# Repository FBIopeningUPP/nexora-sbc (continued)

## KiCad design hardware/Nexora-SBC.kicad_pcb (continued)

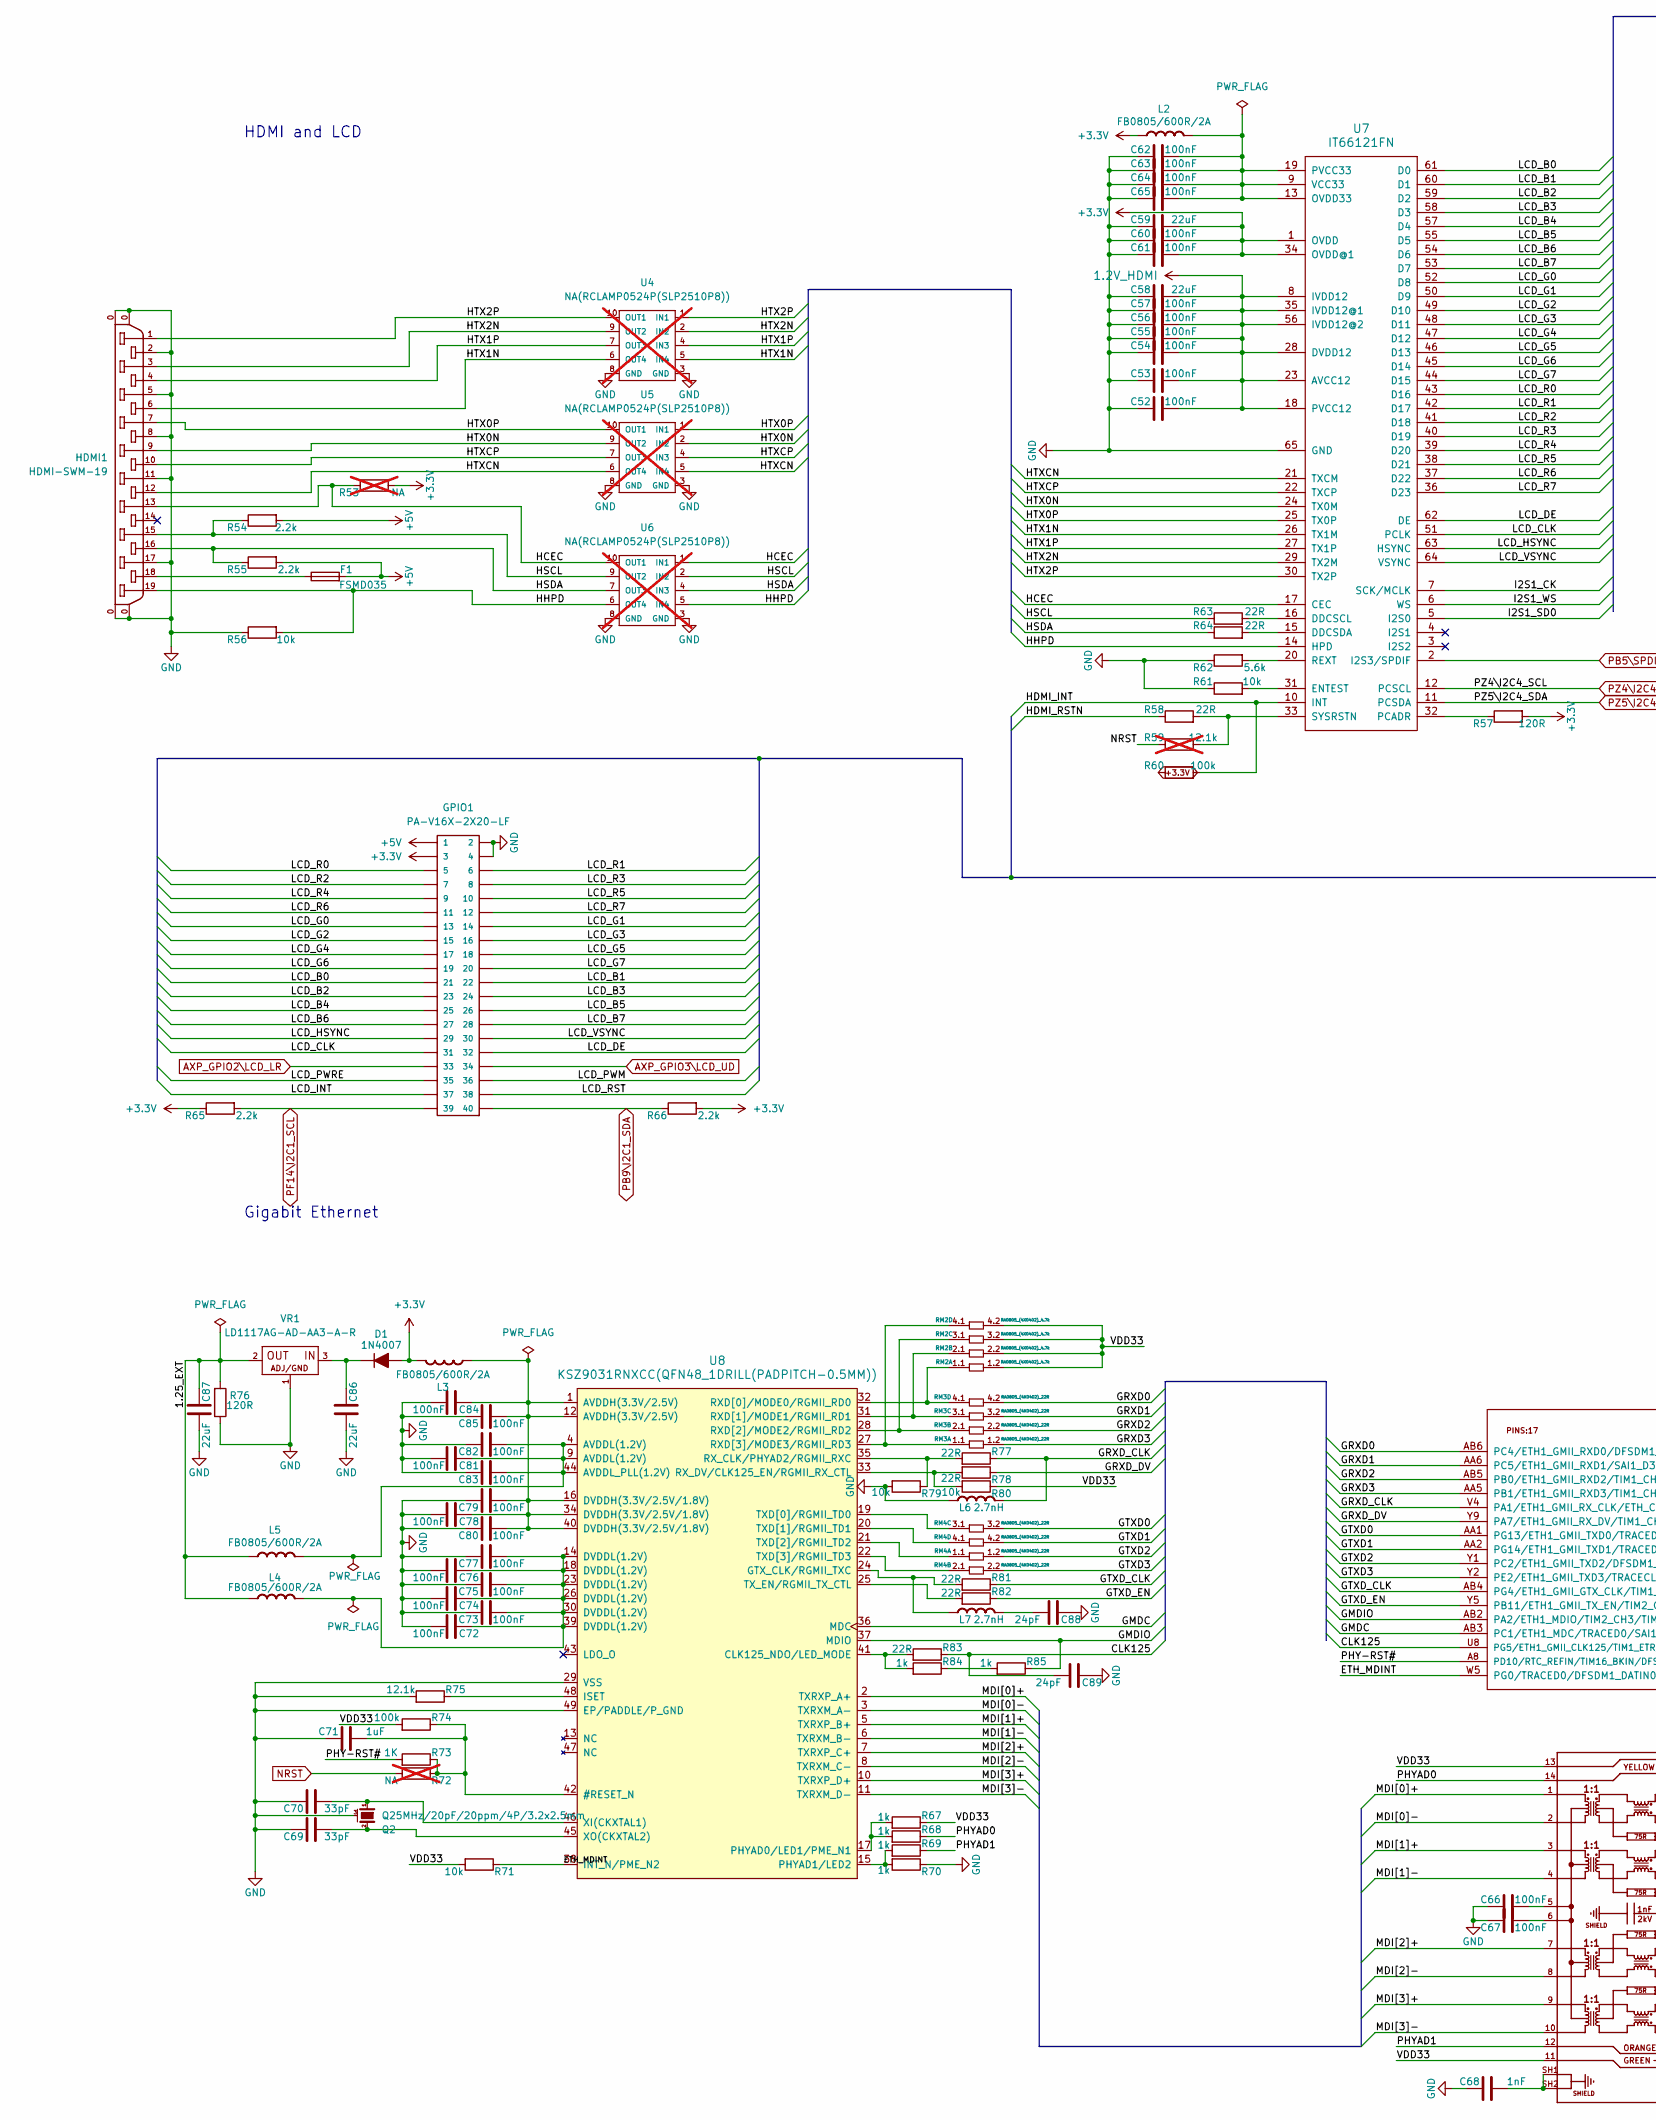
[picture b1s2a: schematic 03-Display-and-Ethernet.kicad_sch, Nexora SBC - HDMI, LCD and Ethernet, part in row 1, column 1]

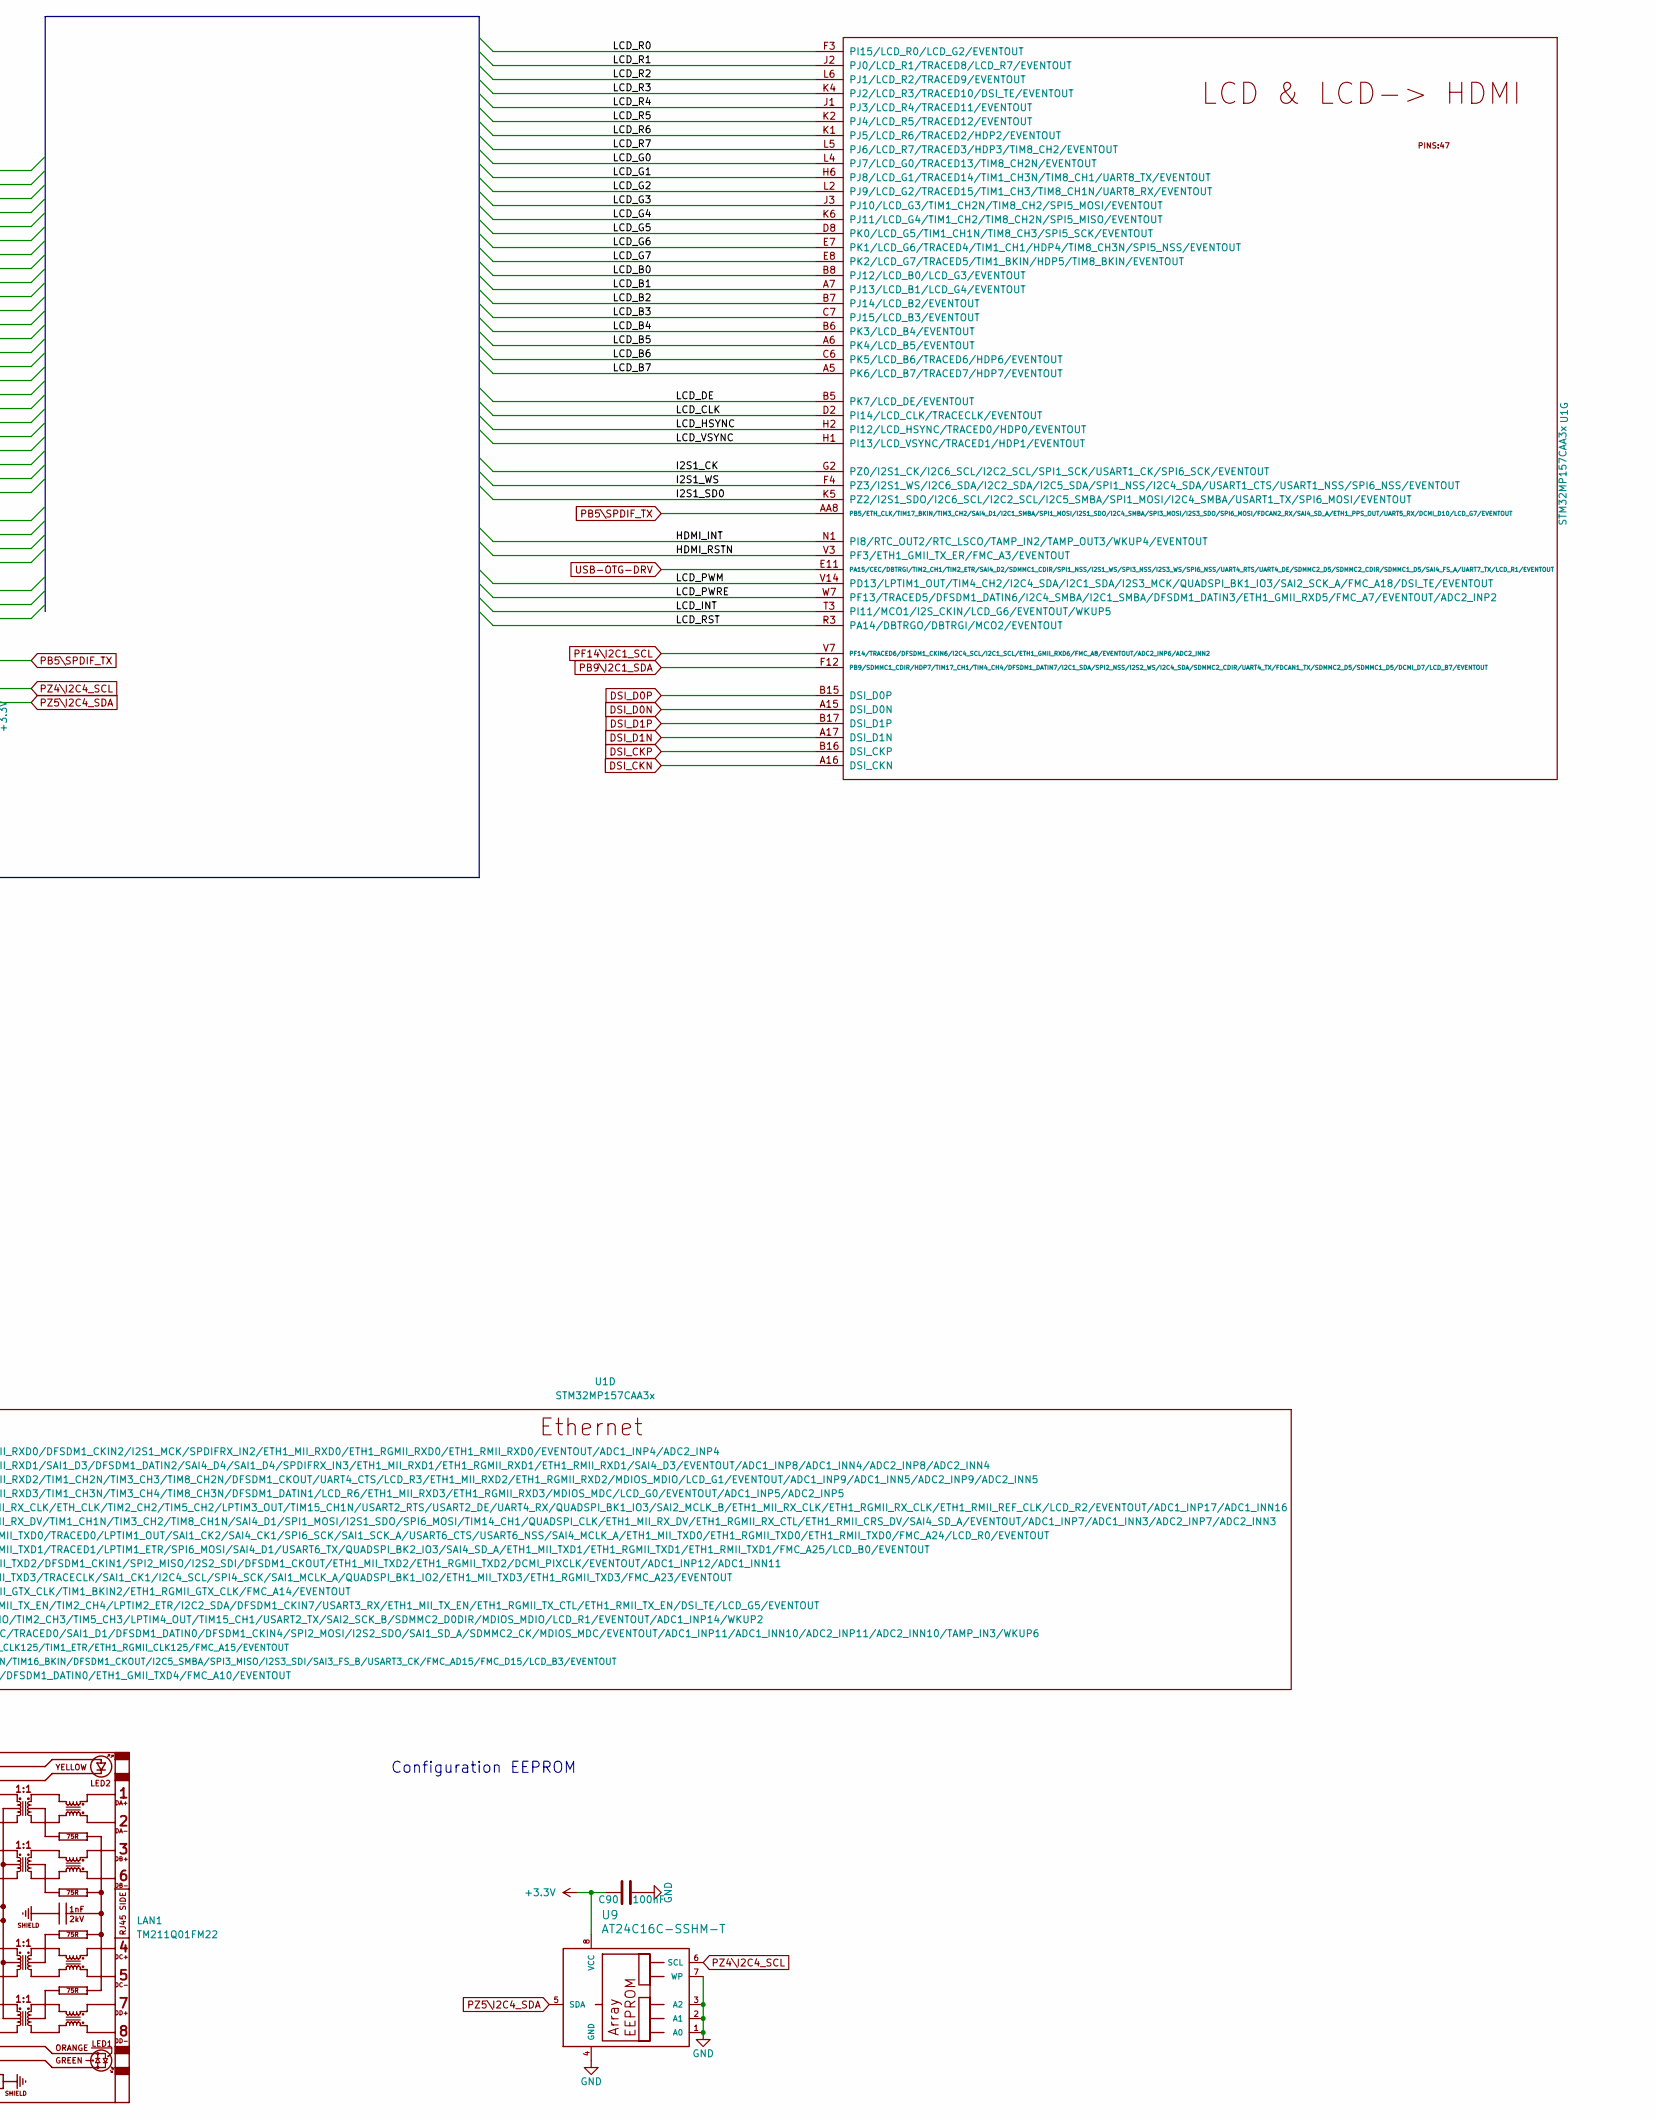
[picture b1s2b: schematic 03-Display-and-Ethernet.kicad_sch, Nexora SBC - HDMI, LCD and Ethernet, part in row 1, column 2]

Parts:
C52, C53, C54, C55, C56, C57, C60, C61, C62, C63, C64, C65, C66, C67, C72, C73, C74, C75, C76, C77, C78, C79, C80, C81, C82, C83, C84, C85, C90: 100nF; C_0402_1005Metric
C58, C59, C86, C87: 22uF; C_0402_1005Metric
C68: 1nF; C_0402_1005Metric
C69, C70: 33pF; C_0402_1005Metric
C71: 1uF; C_0402_1005Metric
C88, C89: 24pF; C_0402_1005Metric
D1: 1N4007; D_SMA
F1: FSMD035; FUSE-1206
GPIO1: PA-V16X-2X20-LF; GPH127SMT-02X20(PA-V16X-2X20-LF)
HDMI1: HDMI-SWM-19
L2, L3, L4, L5: FB0805/600R/2A; L_0805_2012Metric; Rating A
L6, L7: 2.7nH; L_0402_1005Metric; Rating A
LAN1: TM211Q01FM22
Q2: Q25MHz/20pF/20ppm/4P/3.2x2.5mm; TSX-3.2x2.5mm_GND(3)
R53, R72: NA; R_0402_1005Metric; not fitted
R54, R55, R65, R66: 2.2k; R_0402_1005Metric
R56, R61, R71, R79, R80: 10k; R_0402_1005Metric
R57, R76: 120R; R_0402_1005Metric
R58, R63, R64, R77, R78, R81, R82, R83: 22R; R_0402_1005Metric
R59: 12.1k; R_0402_1005Metric; not fitted
R60, R74: 100k; R_0402_1005Metric
R62: 5.6k; R_0402_1005Metric
R67, R68, R69, R70, R84, R85: 1k; R_0402_1005Metric
R73: 1K; R_0402_1005Metric
R75: 12.1k; R_0402_1005Metric
RM2: RA0805_(4X0402)_4.7k; RA0805_(4X0402)_xx_BIGGEROUTPADS
RM3, RM4: RA0805_(4X0402)_22R; RA0805_(4X0402)_xx_BIGGEROUTPADS
U1: STM32MP157CAA3x; LFBGA-448(Pitch-0.8mm_Pad-0.4mm_18x18x1.27mm)
U4, U5, U6: NA(RCLAMP0524P(SLP2510P8)); SLP2510P8_TEST; not fitted
U7: IT66121FN; QFN64_9x9mm_Pitch_0.5mm_65PAD_4.5mm
U8: KSZ9031RNXCC(QFN48_1DRILL(PADPITCH-0.5MM)); QFN48_1DRILL(PADPITCH-0.5MM)
U9: AT24C16C-SSHM-T; SOIC-8_3.9x4.9mm_P1.27mm
VR1: LD1117AG-AD-AA3-A-R; SOT223

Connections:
1.2V_HDMI: C52.2, C53.2, C54.2, C55.2, C56.2, C57.2, C58.2, U7.8 (IVDD12), U7.18 (PVCC12), U7.23 (AVCC12), U7.28 (DVDD12), U7.35 (IVDD12@1), U7.56 (IVDD12@2); also elsewhere on the board
+3.3V: C59.2, C60.2, C61.2, C90.1, D1.2 (A), GPIO1.3, L2.1 (+), L3.1 (+), R53.1, R57.1, R60.2, R65.2, R66.1, U7.1 (OVDD), U7.34 (OVDD@1), U9.8 (VCC); also elsewhere on the board
+5V: F1.2, GPIO1.1, R54.1, R55.1; also elsewhere on the board
/HDMI, LCD and Ethernet/1.25_EXT: C87.1, L4.1 (+), L5.1 (+), R76.1, VR1.2 (OUT)
/HDMI, LCD and Ethernet/CLK125: C89.2, R83.2, U1.U8 (PG5/ETH1_GMII_CLK125/TIM1_ETR/ETH1_RGMI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)
/HDMI, LCD and Ethernet/ETH_MDINT: R71.2, U1.W5 (PG0/TRACED0/DFSDM1_DATIN0/ETH1_GMII_TXD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), U8.38 (INT_N/PME_N2)
/HDMI, LCD and Ethernet/GMDC: U1.AB3 (PC1/ETH1_MDC/TRACED0/SAI1_D1/DFSDM1_DAT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), U8.36 (MDC)
/HDMI, LCD and Ethernet/GMDIO: R85.2, U1.AB2 (PA2/ETH1_MDIO/TIM2_CH3/TIM5_CH3/LPTIM4_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), U8.37 (MDIO)
/HDMI, LCD and Ethernet/GRXD0: RM3.4.2, U1.AB6 (PC4/ETH1_GMII_RXD0/DFSDM1_CKIN2/I2S1_MC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)
/HDMI, LCD and Ethernet/GRXD1: RM3.3.2, U1.AA6 (PC5/ETH1_GMII_RXD1/SAI1_D3/DFSDM1_DATIN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)
/HDMI, LCD and Ethernet/GRXD2: RM3.2.2, U1.AB5 (PB0/ETH1_GMII_RXD2/TIM1_CH2N/TIM3_CH3/T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)
/HDMI, LCD and Ethernet/GRXD3: RM3.1.2, U1.AA5 (PB1/ETH1_GMII_RXD3/TIM1_CH3N/TIM3_CH4/T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)
/HDMI, LCD and Ethernet/GRXD_CLK: L6.2 (-), R77.2, U1.V4 (PA1/ETH1_GMII_RX_CLK/ETH_CLK/ТIM2_CH2/T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)
/HDMI, LCD and Ethernet/GRXD_DV: R78.2, U1.Y9 (PA7/ETH1_GMII_RX_DV/TIM1_CH1N/TIM3_CH2/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)
/HDMI, LCD and Ethernet/GTXD0: RM4.3.2, U1.AA1 (PG13/ETH1_GMII_TXD0/TRACED0/LPTIM1_OUT/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)
/HDMI, LCD and Ethernet/GTXD1: RM4.4.2, U1.AA2 (PG14/ETH1_GMII_TXD1/TRACED1/LPTIM1_ETR/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)
/HDMI, LCD and Ethernet/GTXD2: RM4.1.2, U1.Y1 (PC2/ETH1_GMII_TXD2/DFSDM1_CKIN1/SPI2_MI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)
/HDMI, LCD and Ethernet/GTXD3: RM4.2.2, U1.Y2 (PE2/ETH1_GMII_TXD3/TRACECLK/SAI1_CK1/I2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)
/HDMI, LCD and Ethernet/GTXD_CLK: R81.2, U1.AB4 (PG4/ETH1_GMII_GTX_CLK/TIM1_BKIN2/ETH1_R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)
/HDMI, LCD and Ethernet/GTXD_EN: R82.2, U1.Y5 (PB11/ETH1_GMII_TX_EN/TIM2_CH4/LPTIM2_ET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)
/HDMI, LCD and Ethernet/HCEC: HDMI1.13, R53.2, U6.1 (IN1), U6.10 (OUT1), U7.17 (CEC)
/HDMI, LCD and Ethernet/HDMI_INT: R60.1, U1.N1 (PI8/RTC_OUT2/RTC_LSCO/TAMP_IN2/TAMP_OUT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), U7.10 (INT)
/HDMI, LCD and Ethernet/HDMI_RSTN: R58.2, U1.V3 (PF3/ETH1_GMII_TX_ER/FMC_A3/EVENTOUT)
/HDMI, LCD and Ethernet/HHPD: HDMI1.19, R56.1, U6.5 (IN4), U6.6 (OUT4), U7.14 (HPD)
/HDMI, LCD and Ethernet/HSCL: HDMI1.15, R54.2, R63.2, U6.2 (IN2), U6.9 (OUT2)
/HDMI, LCD and Ethernet/HSDA: HDMI1.16, R55.2, R64.2, U6.4 (IN3), U6.7 (OUT3)
/HDMI, LCD and Ethernet/HTX0N: HDMI1.9, U5.2 (IN2), U5.9 (OUT2), U7.24 (TX0M)
/HDMI, LCD and Ethernet/HTX0P: HDMI1.7, U5.1 (IN1), U5.10 (OUT1), U7.25 (TX0P)
/HDMI, LCD and Ethernet/HTX1N: HDMI1.6, U4.5 (IN4), U4.6 (OUT4), U7.26 (TX1M)
/HDMI, LCD and Ethernet/HTX1P: HDMI1.4, U4.4 (IN3), U4.7 (OUT3), U7.27 (TX1P)
/HDMI, LCD and Ethernet/HTX2N: HDMI1.3, U4.2 (IN2), U4.9 (OUT2), U7.29 (TX2M)
/HDMI, LCD and Ethernet/HTX2P: HDMI1.1, U4.1 (IN1), U4.10 (OUT1), U7.30 (TX2P)
/HDMI, LCD and Ethernet/HTXCN: HDMI1.12, U5.5 (IN4), U5.6 (OUT4), U7.21 (TXCM)
/HDMI, LCD and Ethernet/HTXCP: HDMI1.10, U5.4 (IN3), U5.7 (OUT3), U7.22 (TXCP)
/HDMI, LCD and Ethernet/I2S1_CK: U1.G2 (PZ0/I2S1_CK/I2C6_SCL/I2C2_SCL/SPI1_SCK/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), U7.7 (SCK/MCLK)
/HDMI, LCD and Ethernet/I2S1_SD0: U1.K5 (PZ2/I2S1_SDO/I2C6_SCL/I2C2_SCL/I2C5_SMB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), U7.5 (I2S0)
/HDMI, LCD and Ethernet/I2S1_WS: U1.F4 (PZ3/I2S1_WS/I2C6_SDA/I2C2_SDA/I2C5_SDA/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), U7.6 (WS)
/HDMI, LCD and Ethernet/LCD_B0: GPIO1.21, U1.B8 (PJ12/LCD_B0/LCD_G3/EVENTOUT), U7.61 (D0)
/HDMI, LCD and Ethernet/LCD_B1: GPIO1.22, U1.A7 (PJ13/LCD_B1/LCD_G4/EVENTOUT), U7.60 (D1)
/HDMI, LCD and Ethernet/LCD_B2: GPIO1.23, U1.B7 (PJ14/LCD_B2/EVENTOUT), U7.59 (D2)
/HDMI, LCD and Ethernet/LCD_B3: GPIO1.24, U1.C7 (PJ15/LCD_B3/EVENTOUT), U7.58 (D3)
/HDMI, LCD and Ethernet/LCD_B4: GPIO1.25, U1.B6 (PK3/LCD_B4/EVENTOUT), U7.57 (D4)
/HDMI, LCD and Ethernet/LCD_B5: GPIO1.26, U1.A6 (PK4/LCD_B5/EVENTOUT), U7.55 (D5)
/HDMI, LCD and Ethernet/LCD_B6: GPIO1.27, U1.C6 (PK5/LCD_B6/TRACED6/HDP6/EVENTOUT), U7.54 (D6)
/HDMI, LCD and Ethernet/LCD_B7: GPIO1.28, U1.A5 (PK6/LCD_B7/TRACED7/HDP7/EVENTOUT), U7.53 (D7)
/HDMI, LCD and Ethernet/LCD_CLK: GPIO1.31, U1.D2 (PI14/LCD_CLK/TRACECLK/EVENTOUT), U7.51 (PCLK)
/HDMI, LCD and Ethernet/LCD_DE: GPIO1.32, U1.B5 (PK7/LCD_DE/EVENTOUT), U7.62 (DE)
/HDMI, LCD and Ethernet/LCD_G0: GPIO1.13, U1.L4 (PJ7/LCD_G0/TRACED13/TIM8_CH2N/EVENTOUT), U7.52 (D8)
/HDMI, LCD and Ethernet/LCD_G1: GPIO1.14, U1.H6 (PJ8/LCD_G1/TRACED14/TIM1_CH3N/TIM8_CH1/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), U7.50 (D9)
/HDMI, LCD and Ethernet/LCD_G2: GPIO1.15, U1.L2 (PJ9/LCD_G2/TRACED15/TIM1_CH3/TIM8_CH1N/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), U7.49 (D10)
/HDMI, LCD and Ethernet/LCD_G3: GPIO1.16, U1.J3 (PJ10/LCD_G3/TIM1_CH2N/TIM8_CH2/SPI5_MOS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), U7.48 (D11)
/HDMI, LCD and Ethernet/LCD_G4: GPIO1.17, U1.K6 (PJ11/LCD_G4/TIM1_CH2/TIM8_CH2N/SPI5_MIS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), U7.47 (D12)
/HDMI, LCD and Ethernet/LCD_G5: GPIO1.18, U1.D8 (PK0/LCD_G5/TIM1_CH1N/TIM8_CH3/SPI5_SCK/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), U7.46 (D13)
/HDMI, LCD and Ethernet/LCD_G6: GPIO1.19, U1.E7 (PK1/LCD_G6/TRACED4/TIM1_CH1/HDP4/TIM8_C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), U7.45 (D14)
/HDMI, LCD and Ethernet/LCD_G7: GPIO1.20, U1.E8 (PK2/LCD_G7/TRACED5/TIM1_BKIN/HDP5/TIM8_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), U7.44 (D15)
/HDMI, LCD and Ethernet/LCD_HSYNC: GPIO1.29, U1.H2 (PI12/LCD_HSYNC/TRACED0/HDP0/EVENTOUT), U7.63 (HSYNC)
/HDMI, LCD and Ethernet/LCD_INT: GPIO1.37, U1.T3 (PI11/MCO1/I2S_CKIN/LCD_G6/EVENTOUT/WKUP5)
/HDMI, LCD and Ethernet/LCD_PWM: GPIO1.36, U1.V14 (PD13/LPTIM1_OUT/TIM4_CH2/I2C4_SDA/I2C1_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)
/HDMI, LCD and Ethernet/LCD_PWRE: GPIO1.35, U1.W7 (PF13/TRACED5/DFSDM1_DATIN6/I2C4_SMBA/I2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)
/HDMI, LCD and Ethernet/LCD_R0: GPIO1.5, U1.F3 (PI15/LCD_R0/LCD_G2/EVENTOUT), U7.43 (D16)
/HDMI, LCD and Ethernet/LCD_R1: GPIO1.6, U1.J2 (PJ0/LCD_R1/TRACED8/LCD_R7/EVENTOUT), U7.42 (D17)
/HDMI, LCD and Ethernet/LCD_R2: GPIO1.7, U1.L6 (PJ1/LCD_R2/TRACED9/EVENTOUT), U7.41 (D18)
/HDMI, LCD and Ethernet/LCD_R3: GPIO1.8, U1.K4 (PJ2/LCD_R3/TRACED10/DSI_TE/EVENTOUT), U7.40 (D19)
/HDMI, LCD and Ethernet/LCD_R4: GPIO1.9, U1.J1 (PJ3/LCD_R4/TRACED11/EVENTOUT), U7.39 (D20)
/HDMI, LCD and Ethernet/LCD_R5: GPIO1.10, U1.K2 (PJ4/LCD_R5/TRACED12/EVENTOUT), U7.38 (D21)
/HDMI, LCD and Ethernet/LCD_R6: GPIO1.11, U1.K1 (PJ5/LCD_R6/TRACED2/HDP2/EVENTOUT), U7.37 (D22)
/HDMI, LCD and Ethernet/LCD_R7: GPIO1.12, U1.L5 (PJ6/LCD_R7/TRACED3/HDP3/TIM8_CH2/EVENTO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), U7.36 (D23)
/HDMI, LCD and Ethernet/LCD_RST: GPIO1.38, U1.R3 (PA14/DBTRGO/DBTRGI/MCO2/EVENTOUT)
/HDMI, LCD and Ethernet/LCD_VSYNC: GPIO1.30, U1.H1 (PI13/LCD_VSYNC/TRACED1/HDP1/EVENTOUT), U7.64 (VSYNC)
/HDMI, LCD and Ethernet/MDI[0]+: LAN1.1, U8.2 (TXRXP_A+)
/HDMI, LCD and Ethernet/MDI[0]-: LAN1.2, U8.3 (TXRXM_A-)
/HDMI, LCD and Ethernet/MDI[1]+: LAN1.3, U8.5 (TXRXP_B+)
/HDMI, LCD and Ethernet/MDI[1]-: LAN1.4, U8.6 (TXRXM_B-)
/HDMI, LCD and Ethernet/MDI[2]+: LAN1.7, U8.7 (TXRXP_C+)
/HDMI, LCD and Ethernet/MDI[2]-: LAN1.8, U8.8 (TXRXM_C-)
/HDMI, LCD and Ethernet/MDI[3]+: LAN1.9, U8.10 (TXRXP_D+)
/HDMI, LCD and Ethernet/MDI[3]-: LAN1.10, U8.11 (TXRXM_D-)
/HDMI, LCD and Ethernet/PHY-RST#: R73.1, U1.A8 (PD10/RTC_REFIN/TIM16_BKIN/DFSDM1_CKOUT/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)
/HDMI, LCD and Ethernet/PHYAD0: LAN1.14, R68.2
/HDMI, LCD and Ethernet/PHYAD1: LAN1.12, R69.2
/HDMI, LCD and Ethernet/VDD33: LAN1.11, LAN1.13, R67.2, R71.1, R74.1, R80.2, RM2.1.2, RM2.2.2, RM2.3.2, RM2.4.2
AXP_GPIO2\LCD_LR: GPIO1.33; also elsewhere on the board
AXP_GPIO3\LCD_UD: GPIO1.34; also elsewhere on the board
DSI_CKN: U1.A16 (DSI_CKN); also elsewhere on the board
DSI_CKP: U1.B16 (DSI_CKP); also elsewhere on the board
DSI_D0N: U1.A15 (DSI_D0N); also elsewhere on the board
DSI_D0P: U1.B15 (DSI_D0P); also elsewhere on the board
DSI_D1N: U1.A17 (DSI_D1N); also elsewhere on the board
DSI_D1P: U1.B17 (DSI_D1P); also elsewhere on the board
GND: C52.1, C53.1, C54.1, C55.1, C56.1, C57.1, C58.1, C59.1, C60.1, C61.1, C62.1, C63.1, C64.1, C65.1, C66.1, C67.1, C68.1, C69.1, C70.1, C71.1, C72.2, C73.1, C74.2, C75.1, C76.2, C77.1, C78.2, C79.1, C80.1, C81.2, C82.1, C83.1, C84.2, C85.1, C86.2, C87.2, C88.1, C89.1, C90.2, GPIO1.2, GPIO1.4, HDMI1.0 (22), HDMI1.2, HDMI1.5, HDMI1.8, HDMI1.11, HDMI1.17, L6.1 (+), Q2.3 (case), R56.2, R61.2, R62.2, R70.2, R75.1, R76.2, R79.1, U4.3 (GND), U4.8 (GND), U5.3 (GND), U5.8 (GND), U6.3 (GND), U6.8 (GND), U7.65 (GND), U8.29 (VSS), U8.49 (EP/PADDLE/P_GND), U9.1 (A0), U9.2 (A1), U9.3 (A2), U9.4 (GND), U9.7 (WP), VR1.1 (ADJ/GND); also elsewhere on the board
NRST: R59.2, R72.1; also elsewhere on the board
unnamed: C68.2, LAN1.SH1, LAN1.SH2
unnamed: C86.1, D1.1 (K), VR1.3 (IN)
unnamed: F1.1, HDMI1.18
unnamed: C62.2, C63.2, C64.2, C65.2, L2.2 (-), U7.9 (VCC33), U7.13 (OVDD33), U7.19 (PVCC33)
unnamed: C78.1, C79.2, C80.2, C84.1, C85.2, L3.2 (-), U8.1 (AVDDH(3.3V/2.5V)), U8.12 (AVDDH(3.3V/2.5V)), U8.16 (DVDDH(3.3V/2.5V/1.8V)), U8.34 (DVDDH(3.3V/2.5V/1.8V)), U8.40 (DVDDH(3.3V/2.5V/1.8V))
unnamed: C72.1, C73.2, C74.1, C75.2, C76.1, C77.2, L4.2 (-), U8.14 (DVDDL(1.2V)), U8.18 (DVDDL(1.2V)), U8.23 (DVDDL(1.2V)), U8.26 (DVDDL(1.2V)), U8.30 (DVDDL(1.2V)), U8.39 (DVDDL(1.2V))
unnamed: C81.1, C82.2, C83.2, L5.2 (-), U8.4 (AVDDL(1.2V)), U8.9 (AVDDL(1.2V)), U8.44 (AVDDL_PLL(1.2V))
unnamed: L7.1 (+), R81.1, U8.24 (GTX_CLK/RGMII_TXC)
unnamed: C88.2, L7.2 (-)
unnamed: C66.2, LAN1.5
unnamed: C67.2, LAN1.6
unnamed: R84.2, R85.1
unnamed: R63.1, U7.16 (DDCSCL)
unnamed: R64.1, U7.15 (DDCSDA)
unnamed: R61.1, U7.31 (ENTEST)
unnamed: R57.2, U7.32 (PCADR)
unnamed: R62.1, U7.20 (REXT)
unnamed: R58.1, R59.1, U7.33 (SYSRSTN)
unnamed: C71.2, R72.2, R73.2, R74.2, U8.42 (#RESET_N)
unnamed: R83.1, R84.1, U8.41 (CLK125_NDO/LED_MODE)
unnamed: R75.2, U8.48 (ISET)
unnamed: R67.1, R68.1, U8.17 (PHYAD0/LED1/PME_N1)
unnamed: R69.1, R70.1, U8.15 (PHYAD1/LED2)
unnamed: RM2.1.1, RM3.4.1, U8.32 (RXD[0]/MODE0/RGMII_RD0)
unnamed: RM2.2.1, RM3.3.1, U8.31 (RXD[1]/MODE1/RGMII_RD1)
unnamed: RM2.3.1, RM3.2.1, U8.28 (RXD[2]/MODE2/RGMII_RD2)
unnamed: RM2.4.1, RM3.1.1, U8.27 (RXD[3]/MODE3/RGMII_RD3)
unnamed: R77.1, R79.2, U8.35 (RX_CLK/PHYAD2/RGMII_RXC)
unnamed: R78.1, R80.1, U8.33 (RX_DV/CLK125_EN/RGMII_RX_CTL)
unnamed: RM4.3.1, U8.19 (TXD[0]/RGMII_TD0)
unnamed: RM4.4.1, U8.20 (TXD[1]/RGMII_TD1)
unnamed: RM4.1.1, U8.21 (TXD[2]/RGMII_TD2)
unnamed: RM4.2.1, U8.22 (TXD[3]/RGMII_TD3)
unnamed: R82.1, U8.25 (TX_EN/RGMII_TX_CTL)
unnamed: C70.2, Q2.1, U8.46 (XI(CKXTAL1))
unnamed: C69.2, Q2.2, U8.45 (XO(CKXTAL2))
PB5\SPDIF_TX: U1.AA8 (PB5/ETH_CLK/TIM17_BKIN/TIM3_CH2/SAI4_D1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), U7.2 (I2S3/SPDIF); also elsewhere on the board
PB9\I2C1_SDA: GPIO1.40, R66.2, U1.F12 (PB9/SDMMC1_CDIR/HDP7/TIM17_CH1/TIM4_CH4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); also elsewhere on the board
PF14\I2C1_SCL: GPIO1.39, R65.1, U1.V7 (PF14/TRACED6/DFSDM1_CKIN6/I2C4_SCL/I2C1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); also elsewhere on the board
PZ4\I2C4_SCL: U7.12 (PCSCL), U9.6 (SCL); also elsewhere on the board
PZ5\I2C4_SDA: U7.11 (PCSDA), U9.5 (SDA); also elsewhere on the board
USB-OTG-DRV: U1.E11 (PA15/CEC/DBTRGI/TIM2_CH1/TIM2_ETR/SAI4_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); also elsewhere on the board

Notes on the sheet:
HDMI and LCD
Configuration EEPROM
Gigabit Ethernet
